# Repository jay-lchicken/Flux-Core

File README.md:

# Flux Core Lite
## Why I made this

The goal of this is supposed to make making robots easier. I love to build robots and I realised they often use the same components across multiple different PCBs. These includes Buck-Down Converters, Microcontrollers, Motor drivers.

These PCBs require me to connect them via jumper wires which are very unreliable connections. Hence, this PCB combines the most common components into one PCB. However, the motor driver will be a seperate PCB in another project connected via PH2.0 Connectors (more reliable than normal jumper wires)

## Features
- This PCB features a single LED to indicate power
- It runs on RP2354A so that I do not need to connect external RAM.
- It uses a 12 MHz Crystal Clock
- It includes a reset button and BOOT button
- The PCB has a USBC port for code upload.
- It is also equipped with buck down converters so that I dont need to connect a buck down which is another external component.
- and other common microcontroller features...

## PCB

This is a render of how the PCB looks like

This is the schematic

PCB front layer traces

PCB back layer traces

## Components BOM
| Part Number | Type | LCSC Part # | Provided By | Designator | Qty | Link | Total Price |
| :--- | :--- | :--- | :--- | :--- | :---: | :--- | ---: |
| `PH2.0-8P-LT` | Extended | `C722766` | System | CN2 | 5 | [JLCPCB Parts](https://jlcpcb.com/partdetail/C722766) | $0.3685 |
| `TS-1088-AR02016` | Basic | `C720477` | System | S1, S2 | 10 | [JLCPCB Parts](https://jlcpcb.com/partdetail/C720477) | $0.5160 |
| `0805W8F5102T5E` | Basic | `C17737` | System | R4 | 5 | [JLCPCB Parts](https://jlcpcb.com/partdetail/C17737) | $0.0335 |
| `0805W8F270JT5E` | Extended | `C17594` | System | R5, R6 | 20 | [JLCPCB Parts](https://jlcpcb.com/partdetail/C17594) | $0.0580 |
| `0402WGF330JTCE` | Basic | `C25105` | System | R12 | 5 | [JLCPCB Parts](https://jlcpcb.com/partdetail/C25105) | $0.0055 |
| `CL21A226MAQNNNE` | Basic | `C45783` | System | C12, C19 | 10 | [JLCPCB Parts](https://jlcpcb.com/partdetail/C45783) | $1.0840 |
| `WJ127-5.0-02P-14-00A` | Extended | `C3703` | Customer | J3 | 6 | [JLCPCB Parts](https://jlcpcb.com/partdetail/C3703) | $0.7992 |
| `0402WGF1002TCE` | Basic | `C25744` | System | R9 | 5 | [JLCPCB Parts](https://jlcpcb.com/partdetail/C25744) | $0.0050 |
| `XT60-M.` | Extended | `C98733` | System | U4 | 5 | [JLCPCB Parts](https://jlcpcb.com/partdetail/C98733) | $1.7590 |
| `CC0603KRX7R9BB104` | Basic | `C14663` | System | C18 | 5 | [JLCPCB Parts](https://jlcpcb.com/partdetail/C14663) | $0.0520 |
| `SY8120B1ABC` | Extended | `C88474` | System | U5 | 6 | [JLCPCB Parts](https://jlcpcb.com/partdetail/C88474) | $0.9852 |
| `SWPA4030S3R3MT` | Extended | `C15269` | System | L3 | 9 | [JLCPCB Parts](https://jlcpcb.com/partdetail/C15269) | $0.5499 |
| `2.54-1*4` | Extended | `C5116483` | Customer | 3.3V, GND, VSYS | 16 | [JLCPCB Parts](https://jlcpcb.com/partdetail/C5116483) | $0.4032 |
| `0402CG270J500NT` | Extended | `C1557` | System | C10, C11 | 20 | [JLCPCB Parts](https://jlcpcb.com/partdetail/C1557) | $0.0440 |
| `X322512MSB4SI` | Basic | `C9002` | System | X1 | 5 | [JLCPCB Parts](https://jlcpcb.com/partdetail/C9002) | $0.4770 |
| `CL05A475MP5NRNC` | Basic | `C23733` | System | C17, C21, C22, C23 | 20 | [JLCPCB Parts](https://jlcpcb.com/partdetail/C23733) | $0.2260 |
| `MBR120VLSFT1G` | Extended | `C223608` | System | D1 | 7 | [JLCPCB Parts](https://jlcpcb.com/partdetail/C223608) | $1.5365 |
| `CL05A105KA5NQNC` | Basic | `C52923` | System | C14, C15 | 10 | [JLCPCB Parts](https://jlcpcb.com/partdetail/C52923) | $0.0570 |
| `KT-0603YG` | Extended | `C2289` | System | LED1 | 20 | [JLCPCB Parts](https://jlcpcb.com/partdetail/C2289) | $0.2120 |
| `0402WGF1001TCE` | Basic | `C11702` | System | R11, R2 | 10 | [JLCPCB Parts](https://jlcpcb.com/partdetail/C11702) | $0.0130 |
| `CL05B104KO5NNNC` | Basic | `C1525` | System | C1, C13, C2, C20, C... | 55 | [JLCPCB Parts](https://jlcpcb.com/partdetail/C1525) | $0.1320 |
| `0402WGF5101TCE` | Basic | `C25905` | System | R7, R8 | 10 | [JLCPCB Parts](https://jlcpcb.com/partdetail/C25905) | $0.0140 |
| `SMDRI127-100MT` | Extended | `C9904` | System | L2 | 5 | [JLCPCB Parts](https://jlcpcb.com/partdetail/C9904) | $1.1520 |
| `RP2354A` | Extended | `C41378174` | System | U6 | 5 | [JLCPCB Parts](https://jlcpcb.com/partdetail/C41378174) | $6.2420 |
| `0603WAF680JT5E` | Extended | `C27592` | System | R10 | 20 | [JLCPCB Parts](https://jlcpcb.com/partdetail/C27592) | $0.0260 |
| `AP2112K-3.3TRG1` | Extended | `C51118` | System | U3 | 5 | [JLCPCB Parts](https://jlcpcb.com/partdetail/C51118) | $0.8335 |
| `CL05B103KB5NNNC` | Basic | `C15195` | System | C24 | 5 | [JLCPCB Parts](https://jlcpcb.com/partdetail/C15195) | $0.0185 |
| `USB-TYPE-C-018` | Extended | `C2927038` | System | USB1 | 7 | [JLCPCB Parts](https://jlcpcb.com/partdetail/C2927038) | $0.4445 |
| `XT30UPB-M` | Extended | `C428721` | System | CN1 | 5 | [JLCPCB Parts](https://jlcpcb.com/partdetail/C428721) | $1.3180 |
| `1RC0402F3743` | Extended | `C54530857` | System | R3 | 20 | [JLCPCB Parts](https://jlcpcb.com/partdetail/C54530857) | $0.0360 |
| **Components Subtotal** | | | | | **336** | | **$19.4010** |
| **Assembly Cost** | | | | | | | **$48.6900** |
| **PCB Manufacturing Cost** | | | | | | | **$4.0000** |
| **Shipping** | | | | | | | **$10.0000** |=
| **Grand Total** | | | | | | | **$82.0910** |

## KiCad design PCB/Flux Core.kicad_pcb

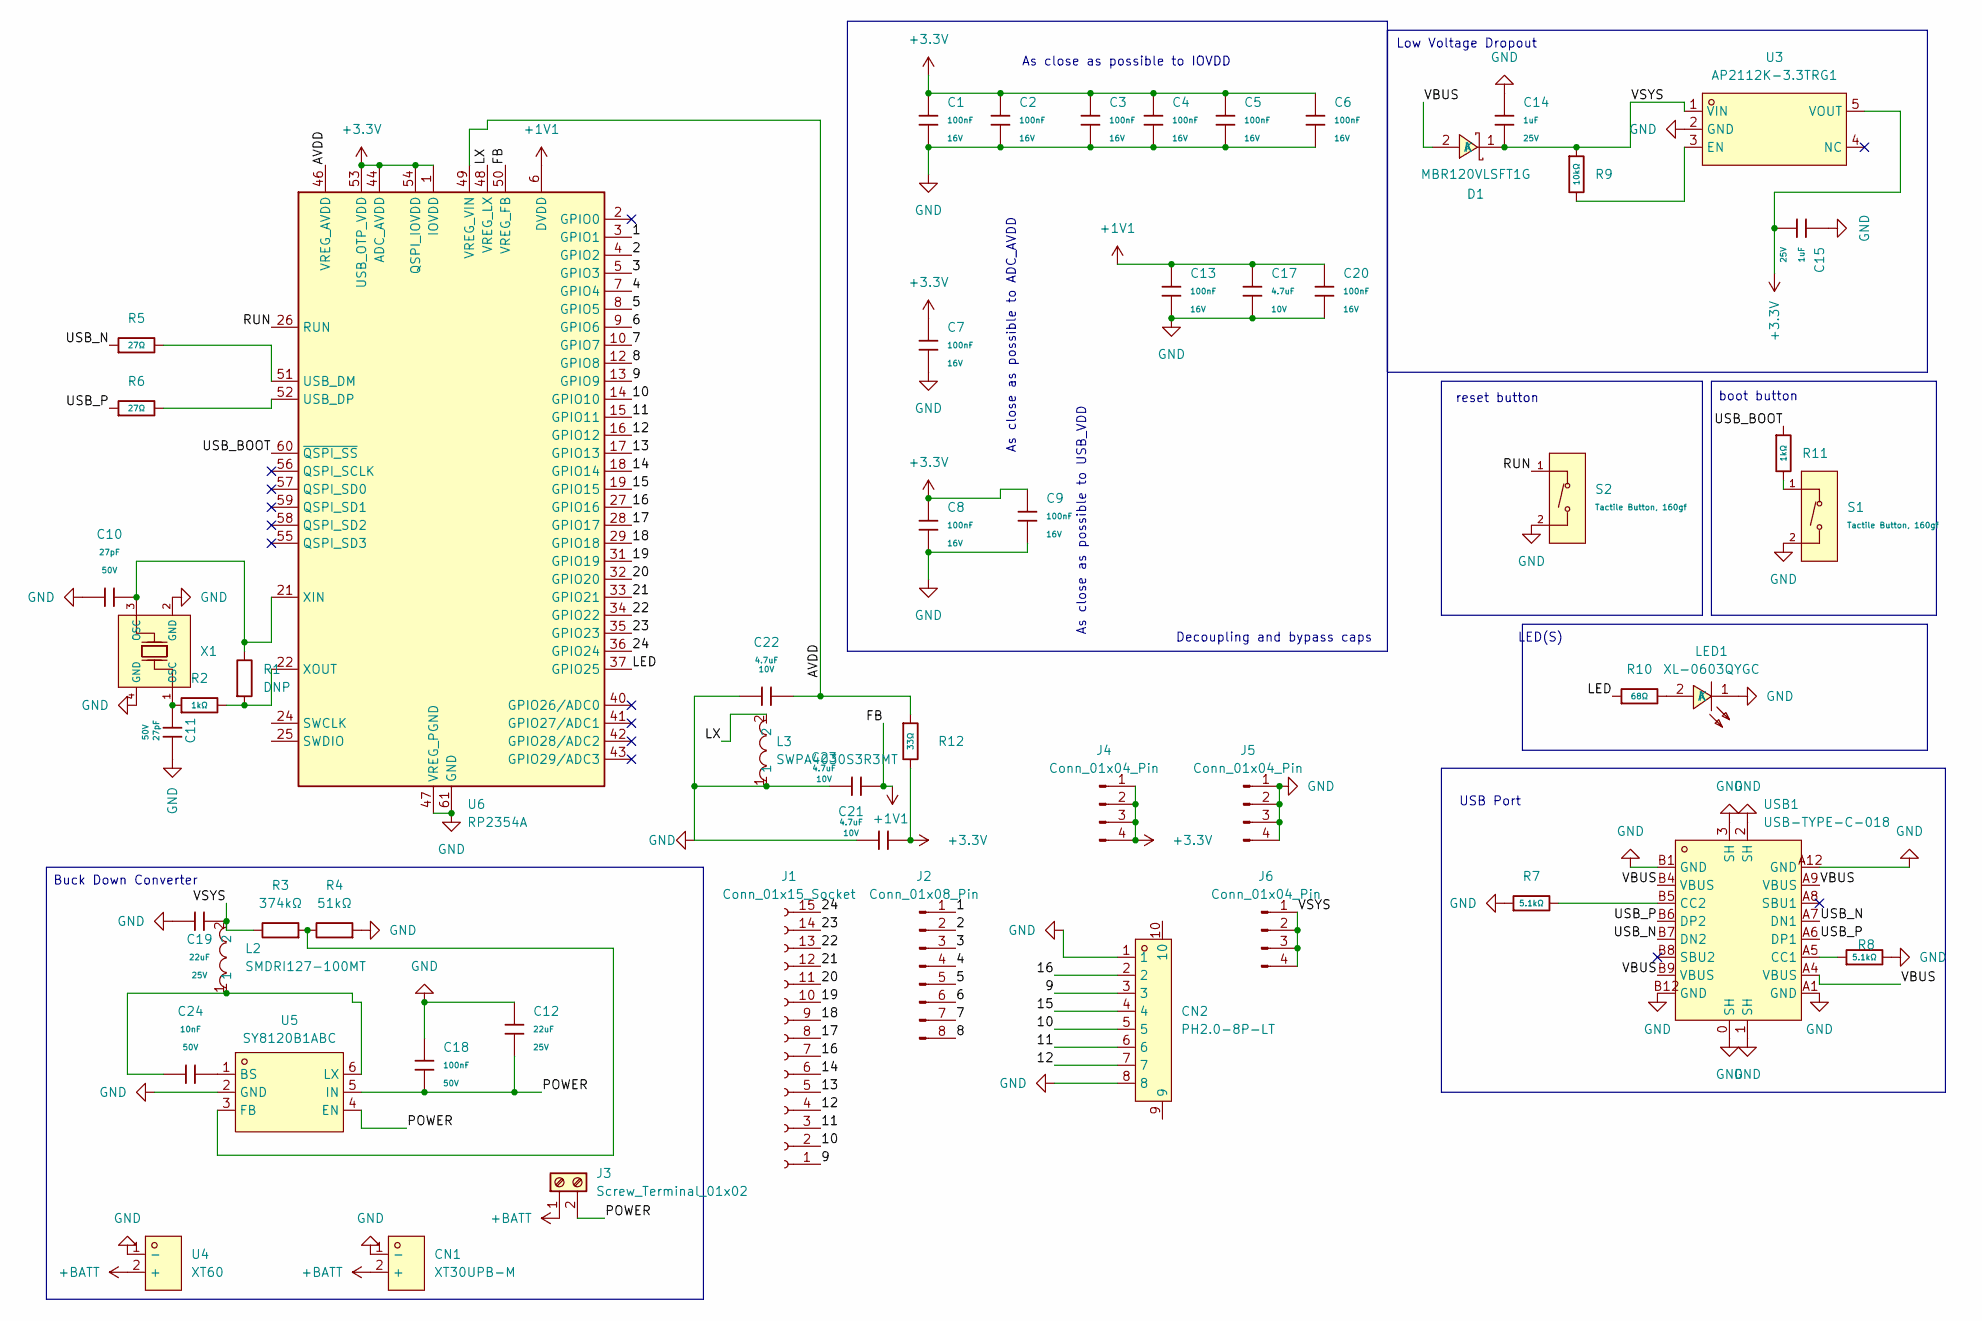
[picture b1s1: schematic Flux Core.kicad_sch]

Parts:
C1, C2, C3, C4, C5, C6, C7, C8, C9, C13, C20: 100nF; C_0402; Voltage Rated 16V; Tolerance ±10%; Part CL05B104KO5NNNC; LCSC C1525
C10, C11: 27pF; C_0402; Voltage Rated 50V; Tolerance ±5%; Part 0402CG270J500NT; LCSC C1557
C12, C19: 22uF; C_0805; Voltage Rated 25V; Tolerance ±20%; Part CL21A226MAQNNNE; LCSC C45783
C14, C15: 1uF; C_0402; Voltage Rated 25V; Tolerance ±10%; Part CL05A105KA5NQNC; LCSC C52923
C17, C21, C22, C23: 4.7uF; C_0402; Voltage Rated 10V; Tolerance ±20%; Part CL05A475MP5NRNC; LCSC C23733
C18: 100nF; C_0603; Voltage Rated 50V; Tolerance ±10%; Part CC0603KRX7R9BB104; LCSC C14663
C24: 10nF; C_0402; Voltage Rated 50V; Tolerance ±10%; Part CL05B103KB5NNNC; LCSC C15195
CN1: XT30UPB-M; CONN-TH_XT30UPB-M; MPN XT30UPB-M; LCSC Part C428721
CN2: PH2.0-8P-LT; CONN-SMD_PH2.0-8P-LT; MPN PH2.0-8P-LT; LCSC Part C722766
D1: MBR120VLSFT1G; SOD-123F_L2.8-W1.8-LS3.7-RD; MPN MBR120VLSFT1G; LCSC Part C223608
J1: Conn_01x15_Socket; PinSocket_1x15_P2.54mm_Vertical
J2: Conn_01x08_Pin; PinHeader_1x08_P2.54mm_Vertical
J3: Screw_Terminal_01x02; Altech_AK100_1x02_P5.00mm
J4, J5, J6: Conn_01x04_Pin; PinSocket_1x04_P2.54mm_Vertical
L2: SMDRI127-100MT; IND-SMD_L12.3-W12.3_SMDRI127; MPN SMDRI127-100MT; LCSC Part C9904
L3: SWPA4030S3R3MT; IND-SMD_L4.0-W4.0_SMNR4012; MPN SWPA4030S3R3MT; LCSC Part C15269
LED1: XL-0603QYGC; LED0603-RD; MPN KT-0603YG; LCSC Part C2289
R1: DNP
R2, R11: 1kΩ; R_0402; Overload Voltage (Max) 50V; Tolerance ±1%; Part 0402WGF1001TCE; LCSC C11702
R3: 374kΩ; R_0402
R4: 51kΩ; R_0805
R5, R6: 27Ω; R_0805; Overload Voltage (Max) 150V; Tolerance ±1%; Part 0805W8F270JT5E; LCSC C17594
R7, R8: 5.1kΩ; R_0402; Overload Voltage (Max) 50V; Tolerance ±1%; Part 0402WGF5101TCE; LCSC C25905
R9: 10kΩ; R_0402; Overload Voltage (Max) 50V; Tolerance ±1%; Part 0402WGF1002TCE; LCSC C25744
R10: 68Ω; R_0603; Overload Voltage (Max) 75V; Tolerance ±1%; Part 0603WAF680JT5E; LCSC C27592
R12: 33Ω; R_0402; Overload Voltage (Max) 50V; Tolerance ±1%; Part 0402WGF330JTCE; LCSC C25105
S1, S2: Tactile Button, 160gf; SW_TS-1088-AR02016; Voltage Rating (Dc) 12V; Part TS-1088-AR02016; LCSC C720477
U3: AP2112K-3.3TRG1; SOT-25-5_L2.9-W1.6-P0.95-LS2.8-BL; MPN AP2112K-3.3TRG1; LCSC Part C51118
U4: XT60; CONN-TH_XT60; MPN XT60-M.; LCSC Part C98733
U5: SY8120B1ABC; SOT-23-6_L2.9-W1.6-P0.95-LS2.8-BL; MPN SY8120B1ABC; LCSC Part C88474
U6: RP2354A; QFN-60-1EP_7x7mm_P0.4mm_EP3.4x3.4mm
USB1: USB-TYPE-C-018; USB-C_SMD-TYPE-C-31-M-12; MPN USB-TYPE-C-018; LCSC Part C2927038
X1: X322512MSB4SI; CRYSTAL-SMD_4P-L3.2-W2.5-BL; Frequency Tolerance ±10ppm; Part X322512MSB4SI; LCSC C9002

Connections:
+1V1: C13.1, C17.1, C20.1, C23.2, U6.6 (DVDD), U6.23 (DVDD), U6.39 (DVDD), U6.50 (VREG_FB)
+3.3V: C1.1, C2.1, C3.1, C4.1, C5.1, C6.1, C7.1, C8.1, C9.1, C15.2, C21.2, J4.1, J4.2, J4.3, J4.4, R12.2, U3.5 (VOUT), U6.1 (IOVDD), U6.11 (IOVDD), U6.20 (IOVDD), U6.30 (IOVDD), U6.38 (IOVDD), U6.44 (ADC_AVDD), U6.45 (IOVDD), U6.53 (USB_OTP_VDD), U6.54 (QSPI_IOVDD); also elsewhere on the board
+BATT: CN1.2 (+), J3.1, U4.2 (+)
/1: J2.1, U6.3 (GPIO1)
/2: J2.2, U6.4 (GPIO2)
/3: J2.3, U6.5 (GPIO3)
/4: J2.4, U6.7 (GPIO4)
/5: J2.5, U6.8 (GPIO5)
/6: J2.6, U6.9 (GPIO6)
/7: J2.7, U6.10 (GPIO7)
/8: J2.8, U6.12 (GPIO8)
/9: CN2.3, J1.1, U6.13 (GPIO9)
/10: CN2.5, J1.2, U6.14 (GPIO10)
/11: CN2.6, J1.3, U6.15 (GPIO11)
/12: CN2.7, J1.4, U6.16 (GPIO12)
/13: J1.5, U6.17 (GPIO13)
/14: J1.6, U6.18 (GPIO14)
/15: CN2.4, U6.19 (GPIO15)
/16: CN2.2, J1.7, U6.27 (GPIO16)
/17: J1.8, U6.28 (GPIO17)
/18: J1.9, U6.29 (GPIO18)
/19: J1.10, U6.31 (GPIO19)
/20: J1.11, U6.32 (GPIO20)
/21: J1.12, U6.33 (GPIO21)
/22: J1.13, U6.34 (GPIO22)
/23: J1.14, U6.35 (GPIO23)
/24: J1.15, U6.36 (GPIO24)
/AVDD: C22.2, R12.1, U6.46 (VREG_AVDD), U6.49 (VREG_VIN)
/LED: R10.1, U6.37 (GPIO25)
/LX: L3.2, U6.48 (VREG_LX)
/POWER: C12.2, C18.2, J3.2, U5.4 (EN), U5.5 (IN)
/RUN: S2.1 (A), U6.26 (RUN)
/USB_BOOT: R11.1, U6.60 (~QSPI_SS)
/USB_N: R5.1, USB1.A7 (DN1), USB1.B7 (DN2)
/USB_P: R6.1, USB1.A6 (DP1), USB1.B6 (DP2)
/VBUS: D1.2 (A), USB1.A4 (VBUS), USB1.A9 (VBUS), USB1.B4 (VBUS), USB1.B9 (VBUS)
/VSYS: C14.2, C19.2, D1.1 (K), J6.1, J6.2, J6.3, J6.4, L2.2, R3.1, R9.1, U3.1 (VIN); also elsewhere on the board
GND: C1.2, C2.2, C3.2, C4.2, C5.2, C6.2, C7.2, C8.2, C9.2, C10.1, C11.1, C12.1, C13.2, C14.1, C15.1, C17.2, C18.1, C19.1, C20.2, C21.1, C22.1, C23.1, CN1.1 (-), CN2.1, CN2.8, J5.1, J5.2, J5.3, J5.4, L3.1, LED1.1 (K), R4.2, R7.1, R8.2, S1.2 (B), S2.2 (B), U3.2 (GND), U4.1 (-), U5.2 (GND), U6.47 (VREG_PGND), U6.61 (GND), USB1.0 (SH), USB1.1 (SH), USB1.2 (SH), USB1.3 (SH), USB1.A1 (GND), USB1.A12 (GND), USB1.B1 (GND), USB1.B12 (GND), X1.2 (GND), X1.4 (GND); also elsewhere on the board
unnamed: C11.2, R2.1, X1.1 (OSC)
unnamed: LED1.2 (A), R10.2
unnamed: R11.2, S1.1 (A)
unnamed: R9.2, U3.3 (EN)
unnamed: C24.2, U5.1 (BS)
unnamed: R3.2, R4.1, U5.3 (FB)
unnamed: C24.1, L2.1, U5.6 (LX)
unnamed: R5.2, U6.51 (USB_DM)
unnamed: R6.2, U6.52 (USB_DP)
unnamed: C10.2, R1.1, U6.21 (XIN), X1.3 (OSC)
unnamed: R1.2, R2.2, U6.22 (XOUT)
unnamed: R8.1, USB1.A5 (CC1)
unnamed: R7.2, USB1.B5 (CC2)

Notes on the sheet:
reset button
LED(S)
As close as possible to ADC_AVDD
USB Port
As close as possible to USB_VDD
Low Voltage Dropout
Decoupling and bypass caps
Buck Down Converter
As close as possible to IOVDD
boot button

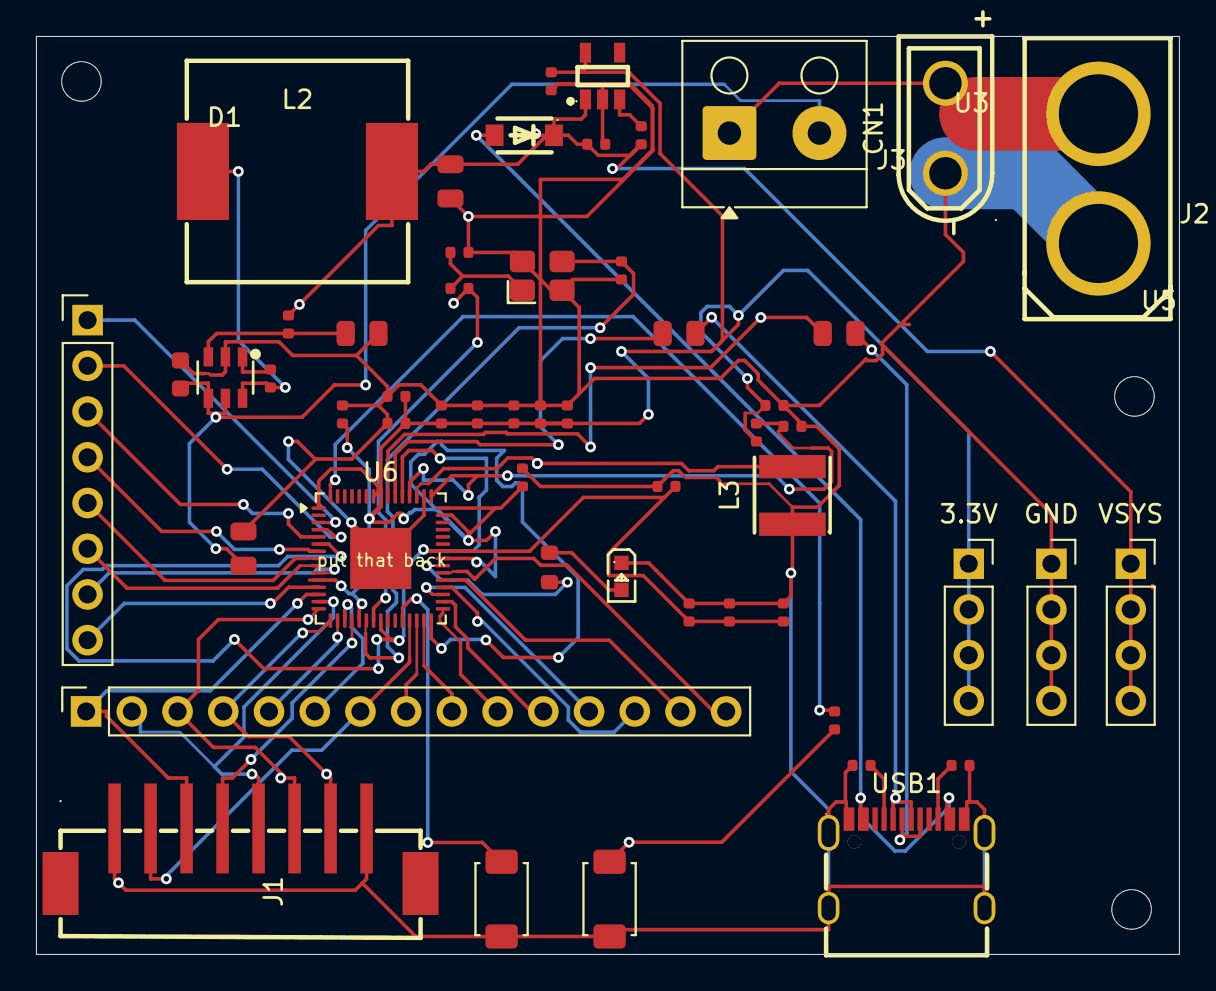
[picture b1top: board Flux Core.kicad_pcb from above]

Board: 2 copper layers, 63.5 x 51.0 mm, 54 parts (0 on the bottom side), 51 nets.

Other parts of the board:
3.3V: Conn_01x04_Pin; PinSocket_1x04_P2.54mm_Vertical
GND: Conn_01x04_Pin; PinSocket_1x04_P2.54mm_Vertical
VSYS: Conn_01x04_Pin; PinSocket_1x04_P2.54mm_Vertical

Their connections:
+3.3V: 3.3V.1, 3.3V.2, 3.3V.3, 3.3V.4; also elsewhere on the board
/VSYS: VSYS.1, VSYS.2, VSYS.3, VSYS.4; also elsewhere on the board
GND: GND.1, GND.2, GND.3, GND.4; also elsewhere on the board

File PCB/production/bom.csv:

Designator,Footprint,Quantity,Value,LCSC Part #
"3.3V, GND, VSYS",PinSocket_1x04_P2.54mm_Vertical,3,Conn_01x04_Pin,
"C1, C13, C2, C20, C3, C4, C5, C6, C7, C8, C9",C_0402,11,100nF,C1525
"C10, C11",C_0402,2,27pF,C1557
"C12, C19",C_0805,2,22uF,C45783
"C14, C15",C_0402,2,1uF,C52923
"C17, C21, C22, C23",C_0402,4,4.7uF,C23733
C18,C_0603,1,100nF,C14663
C24,C_0402,1,10nF,C15195
CN1,CONN-TH_XT30UPB-M,1,XT30UPB-M,C428721
CN2,CONN-SMD_PH2.0-8P-LT,1,PH2.0-8P-LT,C722766
D1,SOD-123F_L2.8-W1.8-LS3.7-RD,1,MBR120VLSFT1G,C223608
J1,PinSocket_1x15_P2.54mm_Vertical,1,Conn_01x15_Socket,
J2,PinHeader_1x08_P2.54mm_Vertical,1,Conn_01x08_Pin,
J3,Altech_AK100_1x02_P5.00mm,1,Screw_Terminal_01x02,
L2,IND-SMD_L12.3-W12.3_SMDRI127,1,SMDRI127-100MT,C9904
L3,IND-SMD_L4.0-W4.0_SMNR4012,1,SWPA4030S3R3MT,C15269
LED1,LED0603-RD,1,XL-0603QYGC,C2289
R10,R_0603,1,68Ω,C27592
"R11, R2",R_0402,2,1kΩ,C11702
R12,R_0402,1,33Ω,C25105
R3,R_0402,1,374kΩ,
R4,R_0805,1,51kΩ,
"R5, R6",R_0805,2,27Ω,C17594
"R7, R8",R_0402,2,5.1kΩ,C25905
R9,R_0402,1,10kΩ,C25744
"S1, S2",SW_TS-1088-AR02016,2,"Tactile Button, 160gf",C720477
U3,SOT-25-5_L2.9-W1.6-P0.95-LS2.8-BL,1,AP2112K-3.3TRG1,C51118
U4,CONN-TH_XT60,1,XT60,C98733
U5,SOT-23-6_L2.9-W1.6-P0.95-LS2.8-BL,1,SY8120B1ABC,C88474
U6,QFN-60-1EP_7x7mm_P0.4mm_EP3.4x3.4mm,1,RP2354A,
USB1,USB-C_SMD-TYPE-C-31-M-12,1,USB-TYPE-C-018,C2927038
X1,CRYSTAL-SMD_4P-L3.2-W2.5-BL,1,X322512MSB4SI,C9002
